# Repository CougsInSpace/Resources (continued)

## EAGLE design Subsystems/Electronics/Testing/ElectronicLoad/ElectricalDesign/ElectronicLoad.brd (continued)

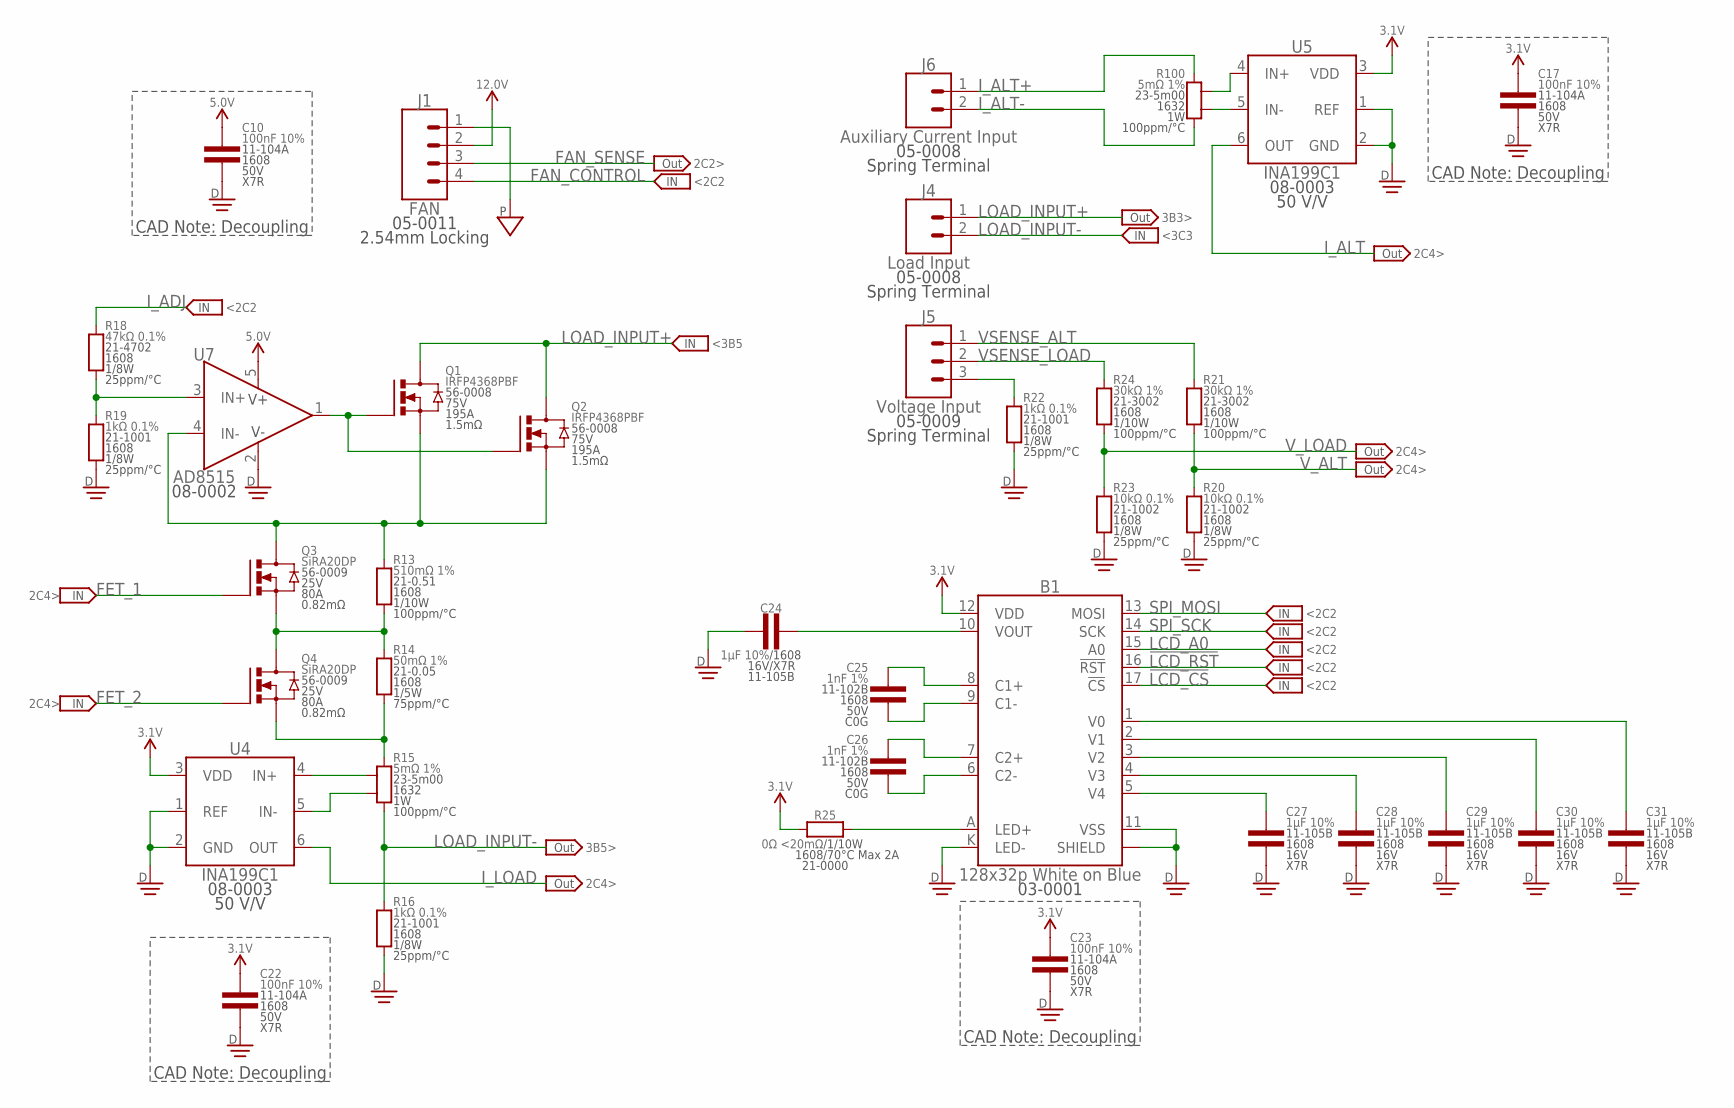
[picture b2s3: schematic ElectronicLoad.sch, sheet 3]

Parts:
B1: 128x32p White on Blue; NHD-C12832A1Z
C10, C17, C22, C23: 100nF 10%; 1608
C24, C27, C28, C29, C30, C31: 1µF 10%; 1608
C25, C26: 1nF 1%; 1608
J1: FAN; THT2.54-1X04-LOCK
J4: Load Input; TERMINAL_SPRING-02
J5: Voltage Input; TERMINAL_SPRING-03
J6: Auxiliary Current Input; TERMINAL_SPRING-02
Q1, Q2: IRFP4368PBF; TO-247-3-DOWN
Q3, Q4: SiRA20DP; POWERPAK-SO-8
R13: 510mΩ 1%; 1608
R14: 50mΩ 1%; 1608
R15, R100: 5mΩ 1%; 1632-KELVIN
R16, R19, R22: 1kΩ 0.1%; 1608
R18: 47kΩ 0.1%; 1608
R20, R23: 10kΩ 0.1%; 1608
R21, R24: 30kΩ 1%; 1608
R25: 0Ω <20mΩ; 1608
U4, U5: INA199C1; SOT363
U7: AD8515; SOT23-5

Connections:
3.1V: B1.12 (VDD), C17.1, C22.1, C23.1, R25.1, U4.3 (VDD), U5.3 (VDD); also elsewhere on the board
5.0V: C10.1, U7.5 (V+); also elsewhere on the board
12.0V: J1.2; also elsewhere on the board
!LCD_CS: B1.17 (!CS); also elsewhere on the board
!LCD_RST: B1.16 (!RST); also elsewhere on the board
C1+: B1.8 (C1+), C25.1
C1-: B1.9 (C1-), C25.2
C2+: B1.7 (C2+), C26.1
C2-: B1.6 (C2-), C26.2
DGND: B1.11 (VSS), B1.CHASSIS@1 (SHIELD), B1.CHASSIS@2 (SHIELD), B1.CHASSIS@3 (SHIELD), B1.CHASSIS@4 (SHIELD), B1.K (LED-), C10.2, C17.2, C22.2, C23.2, C24.1, C27.2, C28.2, C29.2, C30.2, C31.2, R16.1, R19.1, R20.1, R22.1, R23.1, U4.1 (REF), U4.2 (GND), U5.1 (REF), U5.2 (GND), U7.2 (V-); also elsewhere on the board
FAN_CONTROL: J1.4; also elsewhere on the board
FAN_SENSE: J1.3; also elsewhere on the board
FEEDBACK: Q1.3 (S), Q2.3 (S), Q3.5 (D), Q3.6 (D), Q3.7 (D), Q3.8 (D), Q3.PAD (D), R13.2, U7.4 (IN-)
FET_1: Q3.4 (G); also elsewhere on the board
FET_2: Q4.4 (G); also elsewhere on the board
FET_GATE: Q1.1 (G), Q2.1 (G), U7.1 (OUT)
INPUT_SHUNT+: R100.2-KELVIN, U5.4 (IN+)
INPUT_SHUNT-: R100.1-KELVIN, U5.5 (IN-)
I_ADJ: R18.2; also elsewhere on the board
I_ALT: U5.6 (OUT); also elsewhere on the board
I_ALT+: J6.1, R100.2
I_ALT-: J6.2, R100.1
I_LOAD: U4.6 (OUT); also elsewhere on the board
LCD_A0: B1.15 (A0); also elsewhere on the board
LCD_LED: B1.A (LED+), R25.2
LCD_V0: B1.1 (V0), C31.1
LCD_V1: B1.2 (V1), C30.1
LCD_V2: B1.3 (V2), C29.1
LCD_V3: B1.4 (V3), C28.1
LCD_V4: B1.5 (V4), C27.1
LOAD_INPUT+: J4.1, Q1.2 (D), Q1.PAD (D), Q2.2 (D), Q2.PAD (D)
LOAD_INPUT-: J4.2, R15.1, R16.2
OP_AMP_IN: R18.1, R19.2, U7.3 (IN+)
OUTPUT_SHUNT+: R15.2-KELVIN, U4.4 (IN+)
OUTPUT_SHUNT-: R15.1-KELVIN, U4.5 (IN-)
PGND: J1.1; also elsewhere on the board
SHUNT_LOW: Q4.1 (S), Q4.2 (S), Q4.3 (S), R14.1, R15.2
SHUNT_MID: Q3.1 (S), Q3.2 (S), Q3.3 (S), Q4.5 (D), Q4.6 (D), Q4.7 (D), Q4.8 (D), Q4.PAD (D), R13.1, R14.2
SPI_MOSI: B1.13 (MOSI); also elsewhere on the board
SPI_SCK: B1.14 (SCK); also elsewhere on the board
VOUT: B1.10 (VOUT), C24.2
VSENSE_ALT: J5.1, R21.2
VSENSE_GND: J5.3, R22.2
VSENSE_LOAD: J5.2, R24.2
V_ALT: R20.2, R21.1; also elsewhere on the board
V_LOAD: R23.2, R24.1; also elsewhere on the board

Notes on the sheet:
<2C2
2C4>
2C4>
<3B5
3B3>
CAD Note: Decoupling
2C2>
3B5>
<3C3

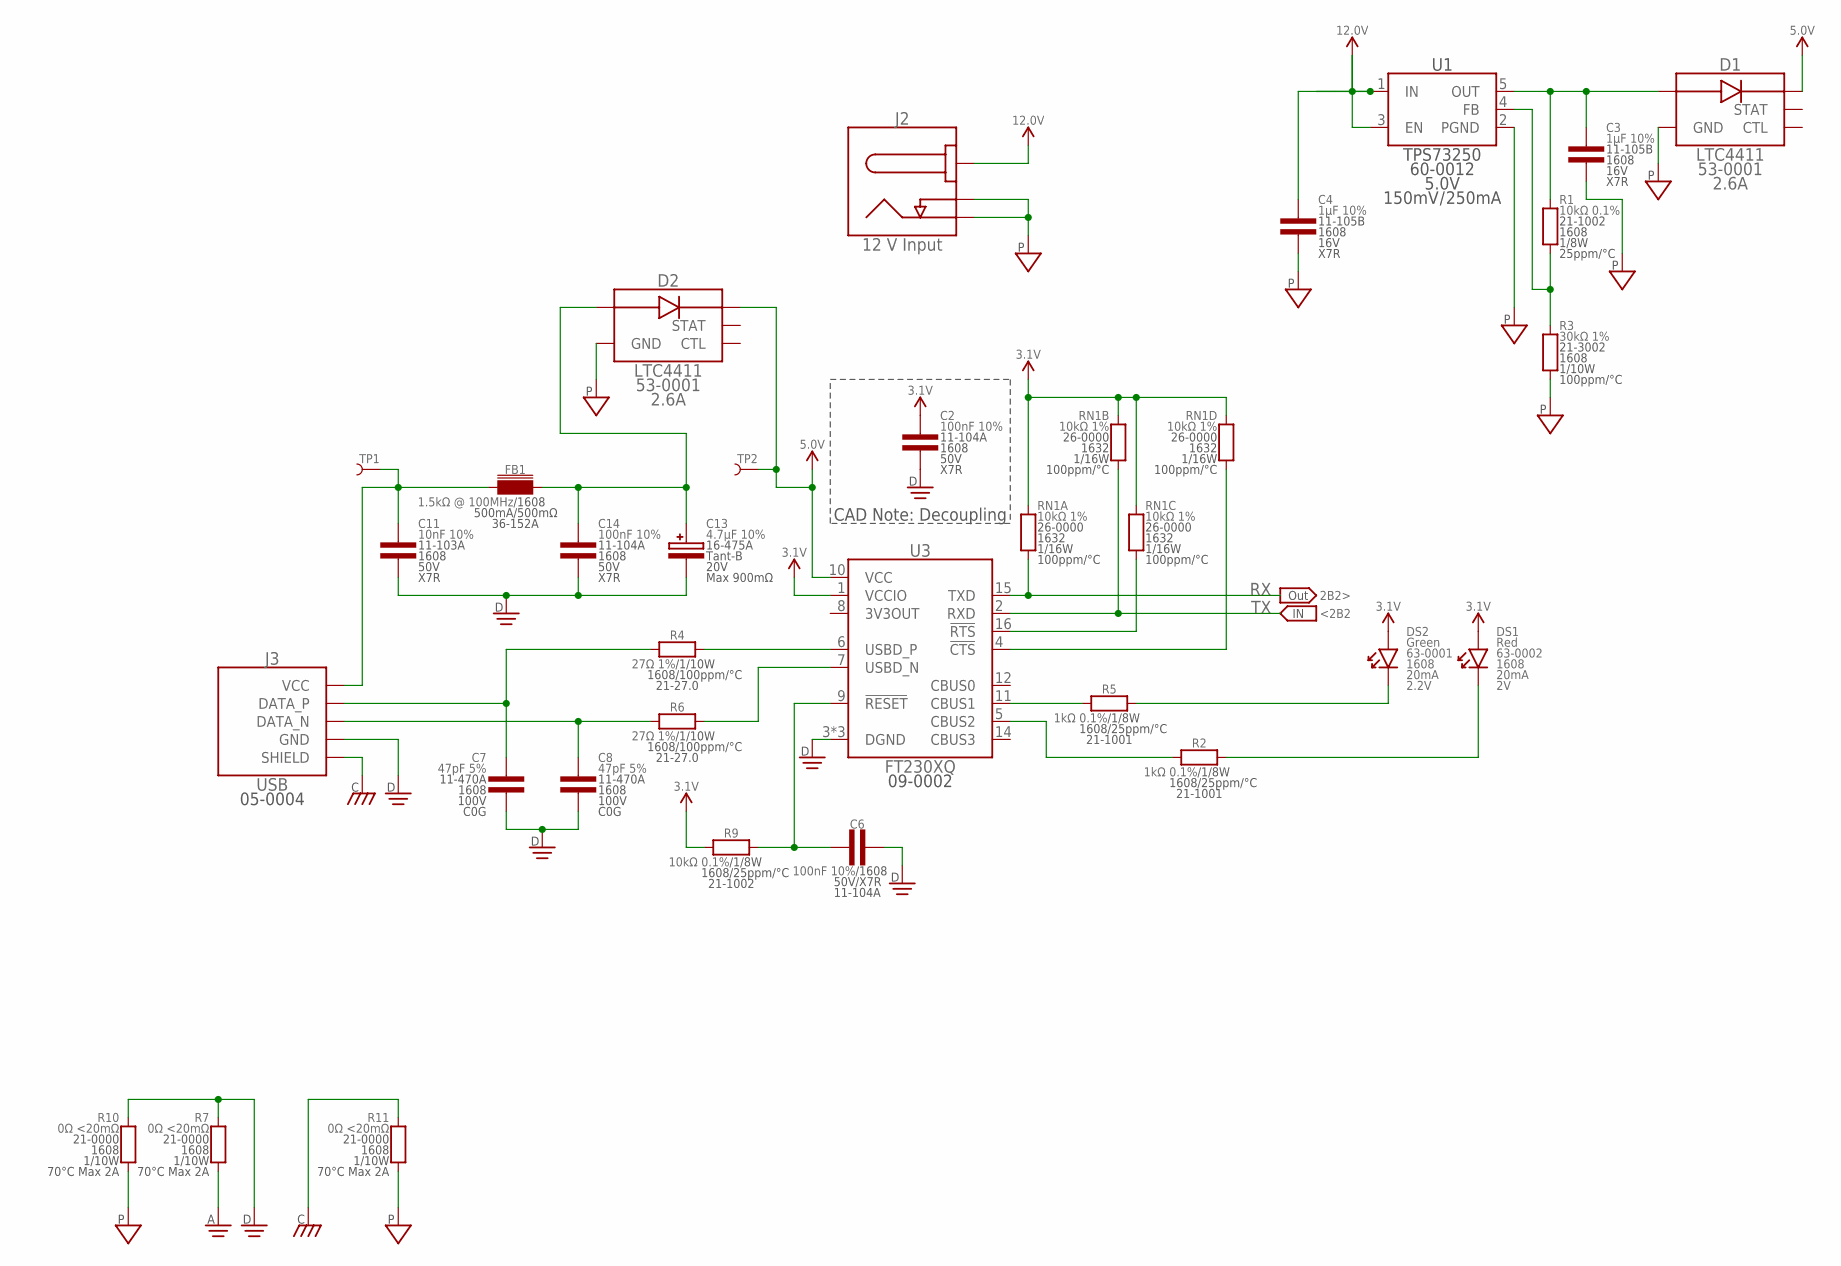
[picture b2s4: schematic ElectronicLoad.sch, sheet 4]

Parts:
C2, C6, C14: 100nF 10%; 1608
C3, C4: 1µF 10%; 1608
C7, C8: 47pF 5%; 1608
C11: 10nF 10%; 1608
C13: 4.7µF 10%; 4028-POL
D1, D2: LTC4411; SOT23-5
DS1: Red; 1608-POL
DS2: Green; 1608-POL
FB1: 1.5kΩ @ 100MHz; 1608
J2: 12 V Input; BARREL-2.1X5.5-R
J3: USB; USB-B-FEMALE
R1, R9: 10kΩ 0.1%; 1608
R2, R5: 1kΩ 0.1%; 1608
R3: 30kΩ 1%; 1608
R4, R6: 27Ω 1%; 1608
R7, R10, R11: 0Ω <20mΩ; 1608
RN1: 10kΩ 1%; 1632
TP1, TP2: TEST_POINT-THT-1.0; THT-1.0
U1: TPS73250; SOT23-5
U3: FT230XQ; QFN-16-4040

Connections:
3.1V: C2.1, DS1.A, DS2.A, R9.1, RN1.5 (2), RN1.6 (2), RN1.7 (2), RN1.8 (2), U3.1 (VCCIO); also elsewhere on the board
5.0V: D1.5 (OUT), D2.5 (OUT), TP2.1, U3.10 (VCC); also elsewhere on the board
12.0V: J2.1 (CENTER); also elsewhere on the board
!CTS: RN1.4 (1), U3.4 (!CTS)
!RTS: RN1.3 (1), U3.16 (!RTS)
AGND: R7.1; also elsewhere on the board
CBUS1: R5.1, U3.11 (CBUS1)
CBUS2: R2.1, U3.5 (CBUS2)
CHASSIS: J3.SHIELD@1 (SHIELD), J3.SHIELD@2 (SHIELD), R11.2; also elsewhere on the board
DGND: C2.2, C6.2, C7.2, C8.2, C11.2, C13.C, C14.2, J3.4 (GND), R7.2, R10.2, U3.3 (DGND), U3.13 (DGND), U3.PAD (DGND); also elsewhere on the board
unnamed: C4.1, U1.1 (IN), U1.3 (EN)
unnamed: C13.A, C14.1, D2.1 (IN), FB1.2
unnamed: C3.1, D1.1 (IN), R1.2, U1.5 (OUT)
unnamed: R1.1, R3.2, U1.4 (FB)
PGND: C3.2, C4.2, D1.2 (GND), D2.2 (GND), J2.2 (SLEEVE), J2.3 (SW), R3.1, R10.1, R11.1, U1.2 (PGND); also elsewhere on the board
RX: RN1.1, U3.15 (TXD); also elsewhere on the board
RXLED_C: DS1.C, R2.2
TX: RN1.2 (1), U3.2 (RXD); also elsewhere on the board
TXLED_C: DS2.C, R5.2
USB5V: C11.1, FB1.1, J3.1 (VCC), TP1.1
USB_CONN_N: C8.1, J3.2 (DATA_N), R6.1
USB_CONN_P: C7.1, J3.3 (DATA_P), R4.1
USB_N: R6.2, U3.7 (USBD_N)
USB_P: R4.2, U3.6 (USBD_P)
USB_RESET: C6.1, R9.2, U3.9 (!RESET)

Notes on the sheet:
CAD Note: Decoupling
2B2>
<2B2

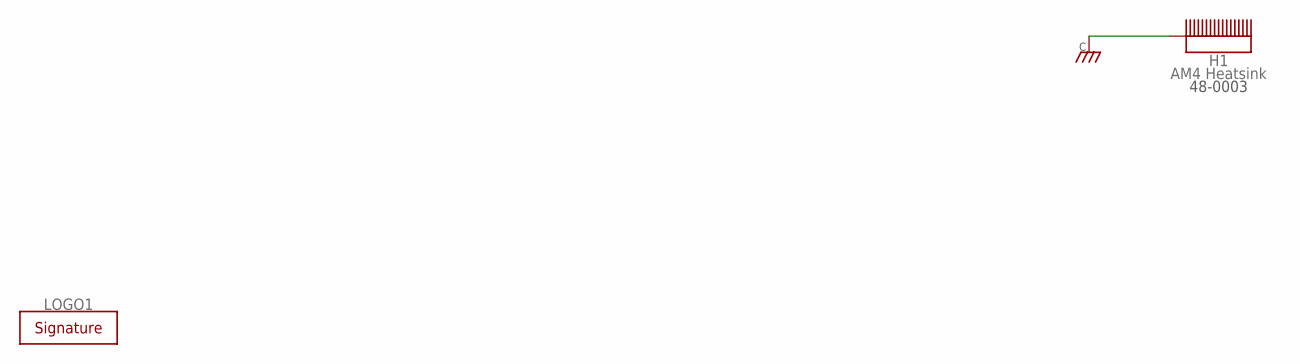
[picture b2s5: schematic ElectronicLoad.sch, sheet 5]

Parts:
H1: AM4 Heatsink; HEATSINK-AM4
LOGO1: SIGNATUREJAYSON; SIGN-JAYSON

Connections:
CHASSIS: H1.1, H1.2, H1.3, H1.4, H1.V1, H1.V2, H1.V3, H1.V4, H1.V5, H1.V6, H1.V7, H1.V8, H1.V9, H1.V10, H1.V11, H1.V12, H1.V13, H1.V14, H1.V15, H1.V16, H1.V17, H1.V18, H1.V19, H1.V20, H1.V21, H1.V22, H1.V23, H1.V24, H1.V25, H1.V26, H1.V27, H1.V28, H1.V29, H1.V30, H1.V31, H1.V32, H1.V33, H1.V34, H1.V35, H1.V36, H1.V37, H1.V38, H1.V39, H1.V40, H1.V41, H1.V42, H1.V43, H1.V44, H1.V45, H1.V46, H1.V47, H1.V48, H1.V49, H1.V50, H1.V51, H1.V52, H1.V53, H1.V54, H1.V55, H1.V56, H1.V57, H1.V58, H1.V59, H1.V60, H1.V61, H1.V62, H1.V63, H1.V64, H1.V65, H1.V66, H1.V67, H1.V68, H1.V69, H1.V70, H1.V71, H1.V72; also elsewhere on the board

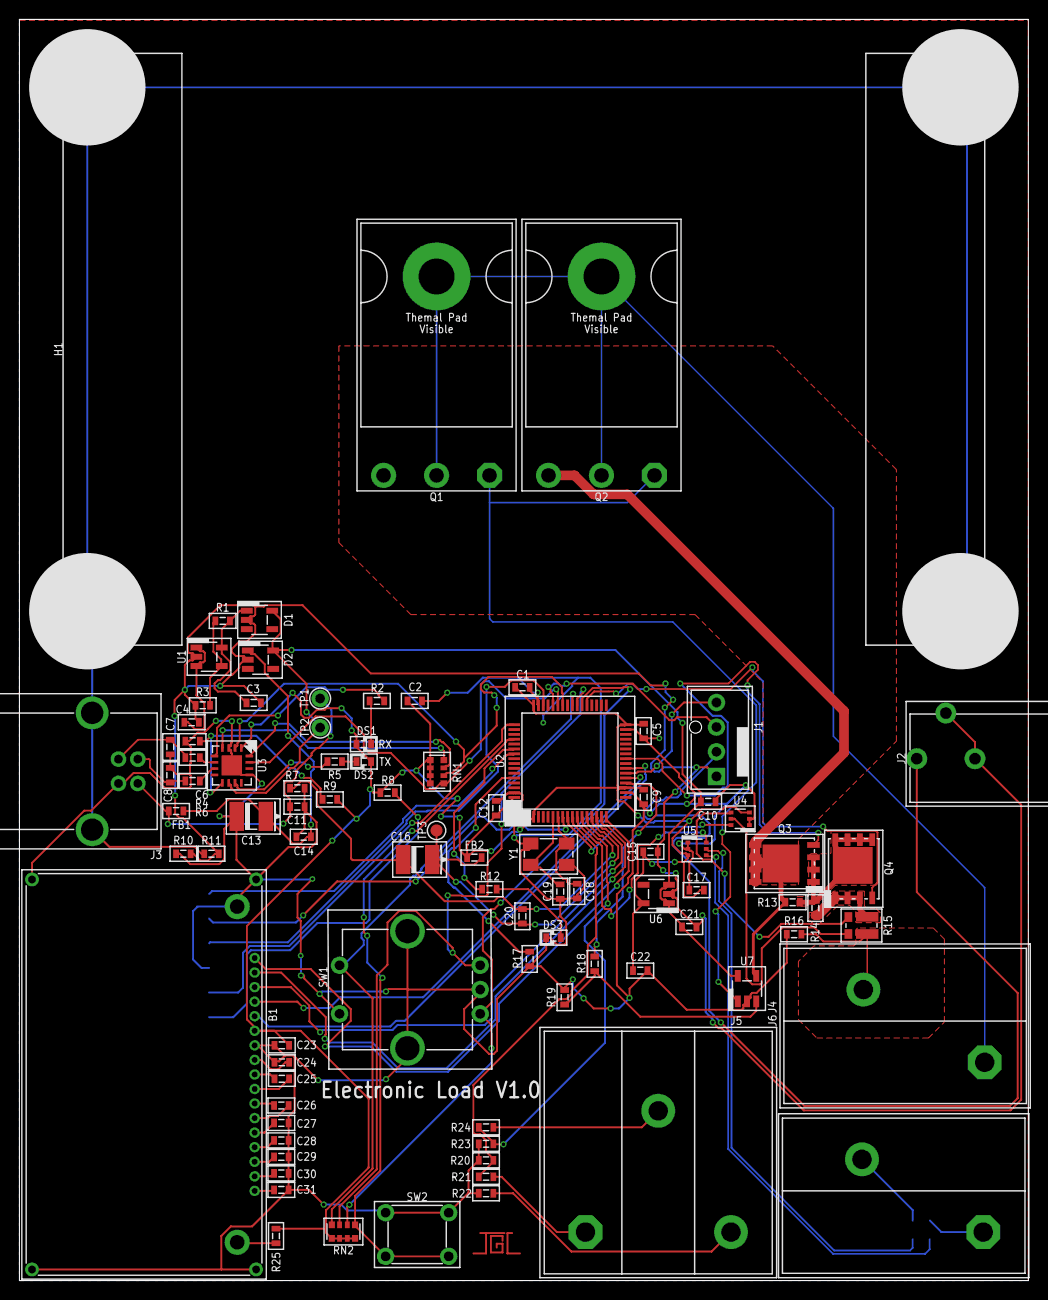
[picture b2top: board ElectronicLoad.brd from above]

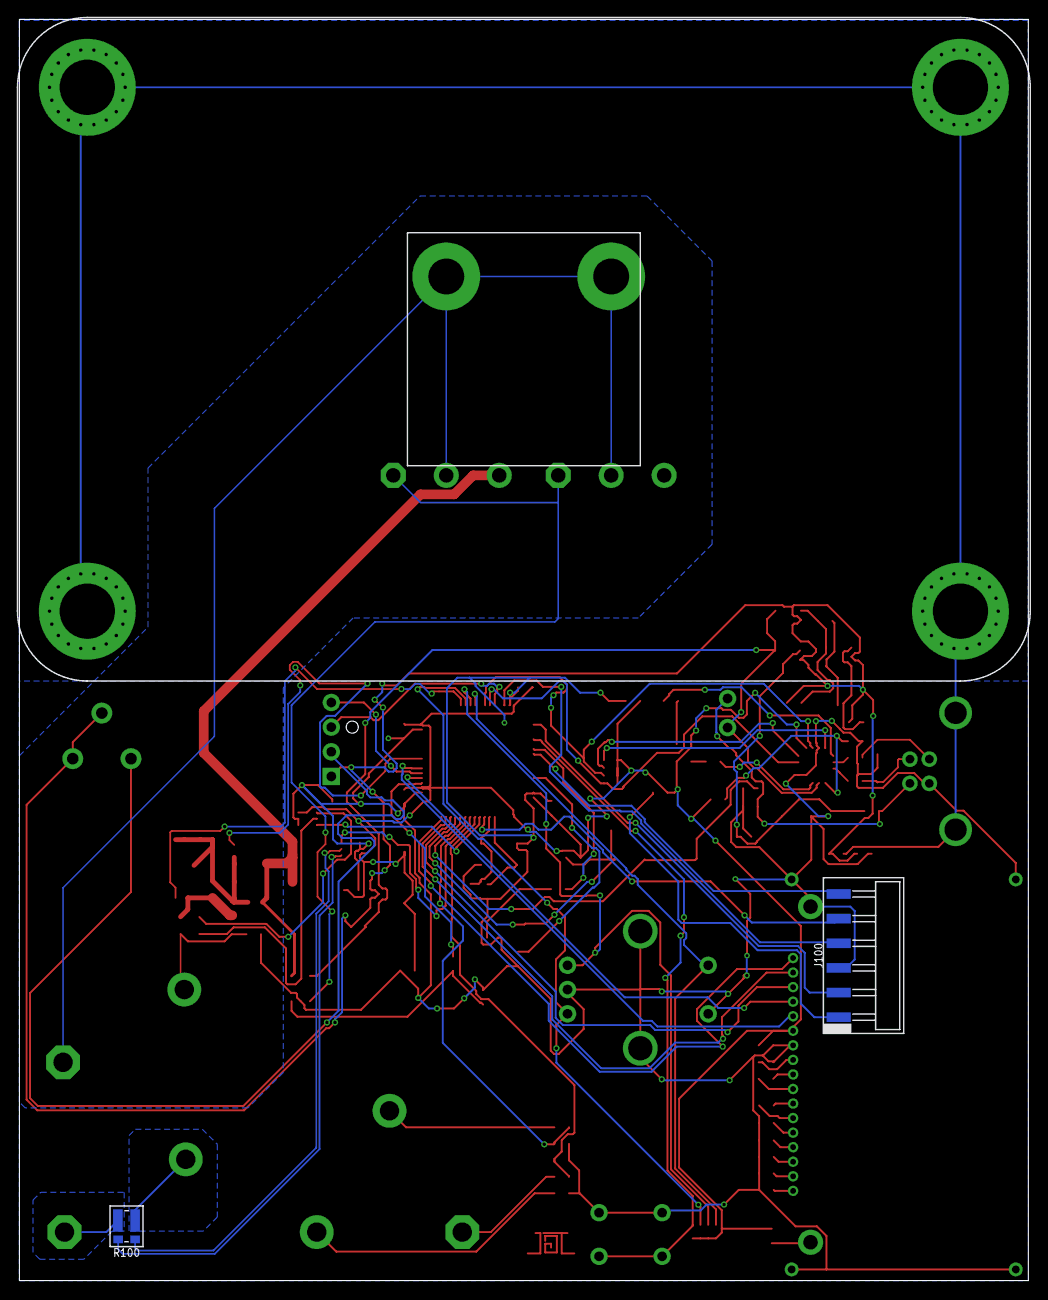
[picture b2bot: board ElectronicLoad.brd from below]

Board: 2 copper layers, 104.0 x 130.0 mm, 93 parts (2 on the bottom side), 81 nets.

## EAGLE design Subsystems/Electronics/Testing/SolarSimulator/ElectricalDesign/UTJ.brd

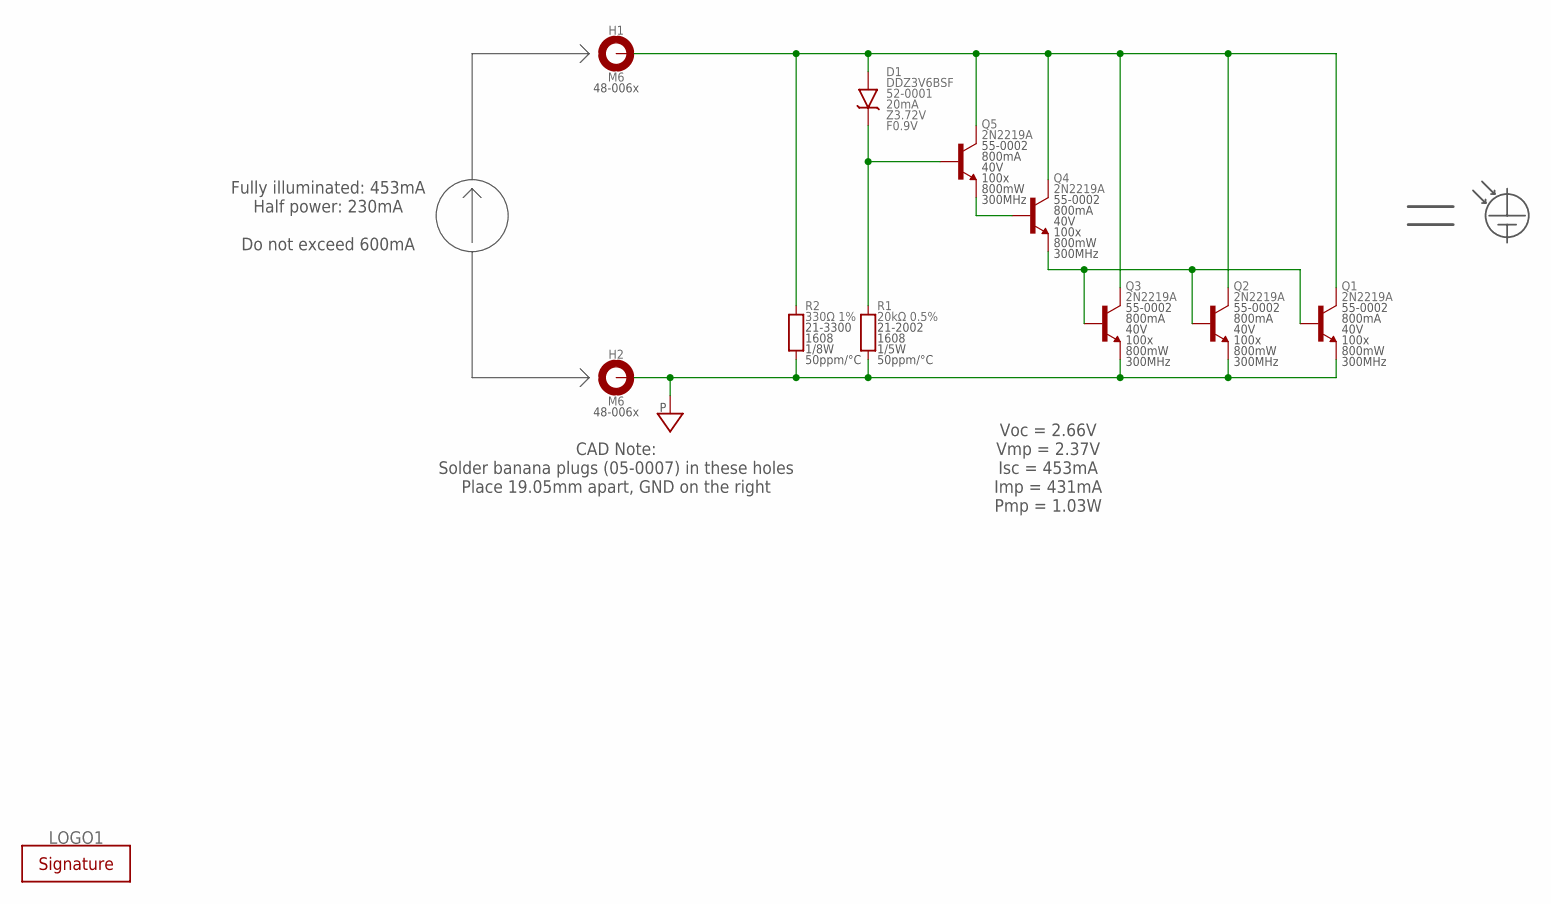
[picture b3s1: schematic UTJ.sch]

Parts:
D1: DDZ3V6BSF; SOD323F
H1, H2: M6; MOUNTING_HOLE-6.6
LOGO1: SIGNATUREBRADLEY; SIGN-BRADLEY
Q1, Q2, Q3, Q4, Q5: 2N2219A; TO-39
R1: 20kΩ 0.5%; 1608
R2: 330Ω 1%; 1608

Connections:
CELL+: D1.A, H1.1, H1.V1, H1.V2, H1.V3, H1.V4, H1.V5, H1.V6, H1.V7, H1.V8, H1.V9, H1.V10, H1.V11, H1.V12, H1.V13, H1.V14, H1.V15, H1.V16, Q1.3 (C), Q2.3 (C), Q3.3 (C), Q4.3 (C), Q5.3 (C), R2.2
EMITTER-1: Q4.2 (B), Q5.1 (E)
EMITTER-2: Q1.2 (B), Q2.2 (B), Q3.2 (B), Q4.1 (E)
PGND: H2.1, H2.V1, H2.V2, H2.V3, H2.V4, H2.V5, H2.V6, H2.V7, H2.V8, H2.V9, H2.V10, H2.V11, H2.V12, H2.V13, H2.V14, H2.V15, H2.V16, Q1.1 (E), Q2.1 (E), Q3.1 (E), R1.1, R2.1
ZENER_C: D1.C, Q5.2 (B), R1.2

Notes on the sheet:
Fully illuminated: 453mA Half power: 230mA Do not exceed 600mA
Voc = 2.66V Vmp = 2.37V Isc = 453mA Imp = 431mA Pmp = 1.03W
CAD Note: Solder banana plugs (05-0007) in these holes Place 19.05mm apart, GND on the right

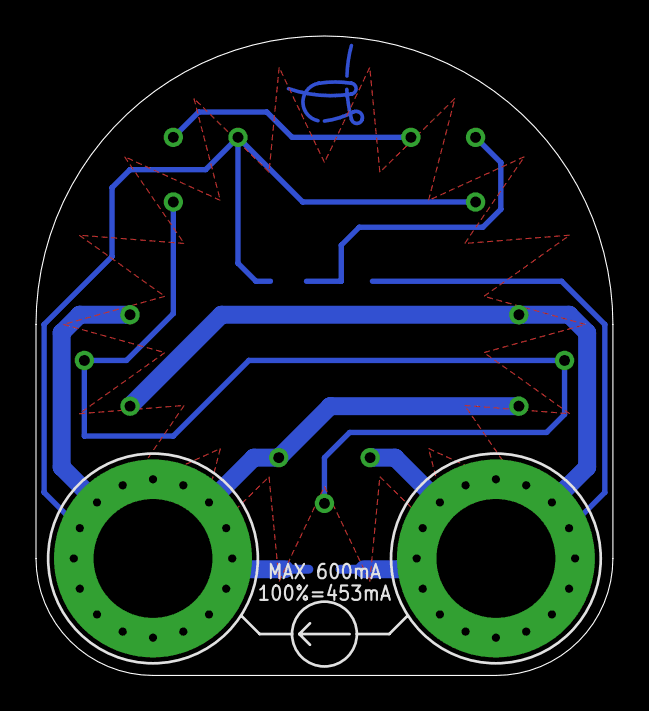
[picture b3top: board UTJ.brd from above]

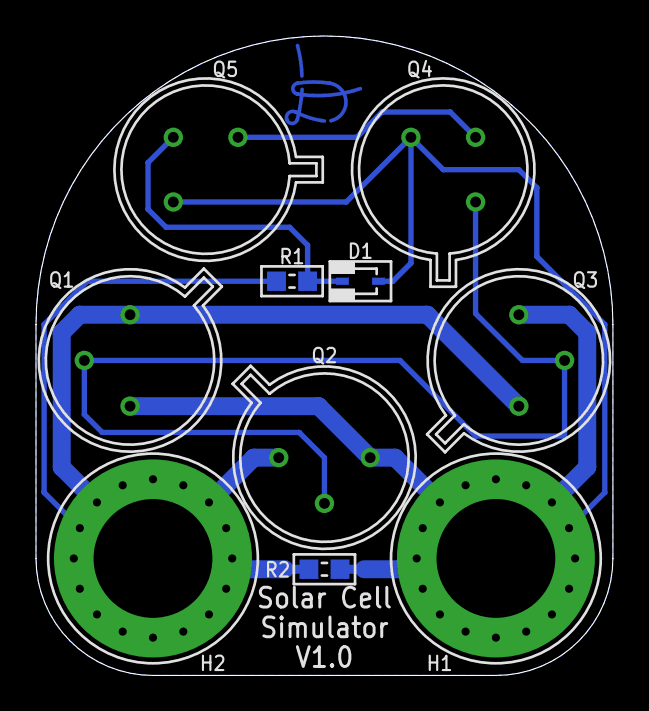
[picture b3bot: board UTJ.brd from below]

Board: 2 copper layers, 32.0 x 35.5 mm, 11 parts (9 on the bottom side), 5 nets.

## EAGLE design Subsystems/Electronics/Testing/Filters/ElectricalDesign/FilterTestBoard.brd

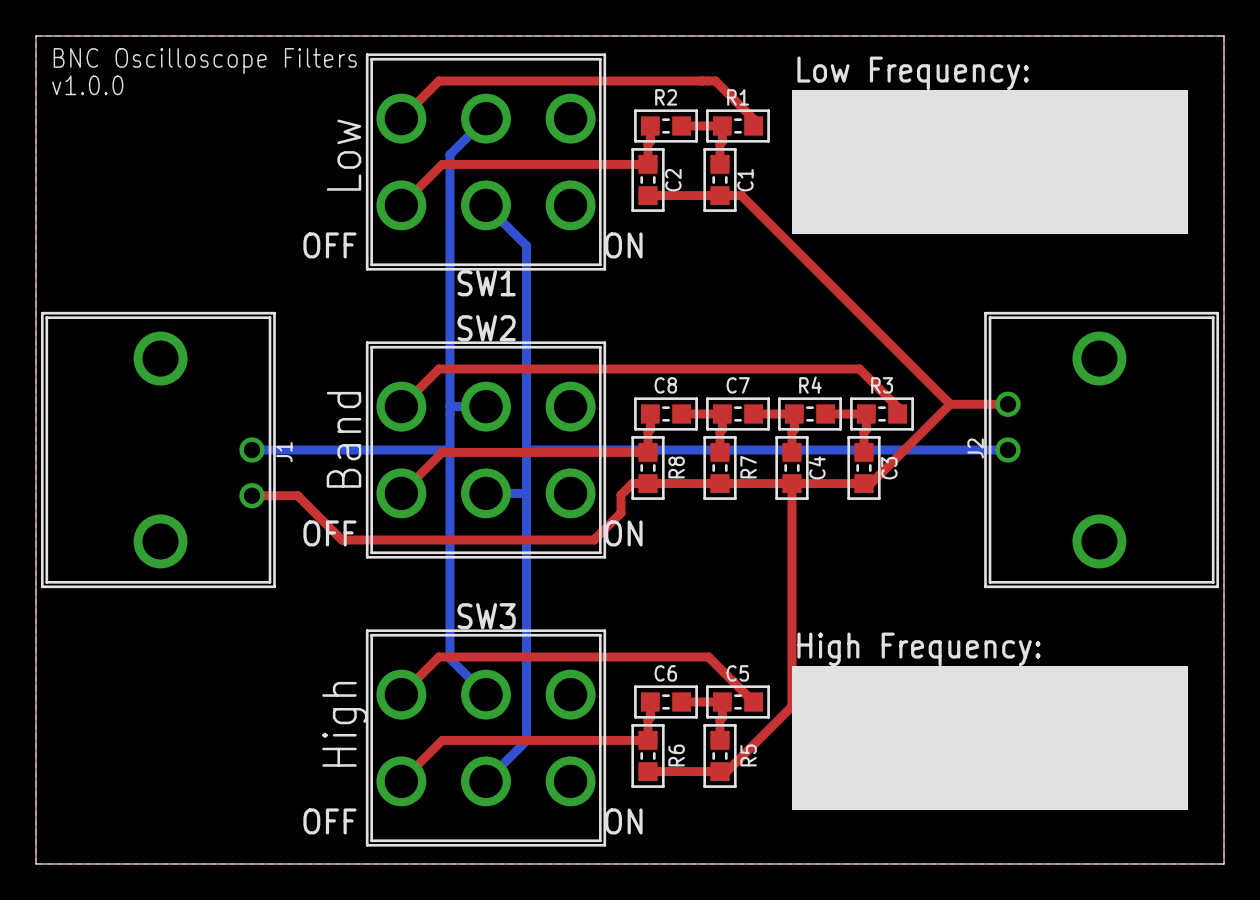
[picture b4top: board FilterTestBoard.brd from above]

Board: 2 copper layers, 66.0 x 46.0 mm, 21 parts (0 on the bottom side), 14 nets.

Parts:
C1, C2, C3, C4, C5, C6, C7, C8: 10µF 10%; 1608
J1, J2: BNC-T-R
R1, R2, R7, R8: 158kΩ 0.1%; 1608
R3, R4, R5, R6: 158Ω 1%; 1608
SW1, SW2, SW3: 100DP1T1B1M2QE

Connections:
BAND_IN: R3.1, SW2.1-B
BAND_INT0: C3.1, R3.2, R4.1
BAND_INT1: C4.1, C7.1, R4.2
BAND_INT2: C7.2, C8.1, R7.2
BAND_OUT: C8.2, R8.2, SW2.1-A
HIGH_IN: C5.1, SW3.1-B
HIGH_INT: C5.2, C6.1, R5.2
HIGH_OUT: C6.2, R6.2, SW3.1-A
INPUT: J1.CENTER, SW1.COM-B, SW2.COM-B, SW3.COM-B
LOW_IN: R1.1, SW1.1-B
LOW_INT: C1.1, R1.2, R2.1
LOW_OUT: C2.1, R2.2, SW1.1-A
OUTPUT: J2.CENTER, SW1.COM-A, SW2.COM-A, SW3.COM-A
PGND: C1.2, C2.2, C3.2, C4.2, J1.SHIELD, J2.SHIELD, R5.1, R6.1, R7.1, R8.1

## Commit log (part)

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2018-04-08 Added Documents
2018-04-12 Updated Header Boxes Layout
2018-04-13 Readme.txt
2018-05-12 Updated Template
2018-05-13 Added Components
2018-05-18 Added Empty Libraries
2018-05-18 Update README.md
    Changed silkscreen line width
2018-05-19 Added Aesthetic Parts
2018-05-19 Added Energy Parts
2018-05-19 Added Signatures
2018-05-20 Added Clocks
2018-05-21 Added Coils
2018-05-21 Added Connectors
2018-05-22 Added Discrete Semiconductors
2018-05-22 Added Fuses
2018-05-22 Added Amplifiers, Comms, & Conversion ICs
    Also fixed some packages' name layer
2018-05-22 Added Logic ICs
2018-05-22 Added Memory
2018-05-22 Added Switches
2018-05-23 Added Power ICs
2018-05-23 Added µControllers
2018-05-23 Added Sensors and a Logic IC
2018-05-24 Added Resistors, RF, LEDs, and Horizontal Symbols
2018-05-24 Added Eagle Guidelines Readme
2018-05-25 Adjusted Title Block and Courtyard
2018-05-25 Updated Title Block Image
2018-05-25 Added Off Sheet Connector Image for Readme
2018-05-27 Added Diagram Components
2018-05-27 Added Through Hole Test Points
2018-05-29 Added PicoLock Connectors
2018-05-30 Added Bolts and TO220 Resistor
2018-05-31 readme
2018-06-01 SDS sheets for current EME 107 lab chemicals
2018-06-03 Added CougSat Bus Symbol
2018-06-04 Added Umbilical Connector
2018-06-05 Adjusted Packages
2018-06-05 Added SWD Connector
2018-06-10 Added Jumper
2018-06-10 Added Dual MOSFETs
2018-06-28 Created Project Management SOP
2018-06-28 Fixed Missing Punctuation
2018-06-28 added file manager script
2018-06-28 Delete README
    will make new one
2018-07-04 Created Inventor Templates
2018-07-17 Added Component Models and Updated Eagle Library Font
2018-07-20 added file deletion functionality
2018-07-22 Added Parts
2018-07-22 Added Acronyms
2018-07-22 Adjusted Symbol Layout
2018-07-23 Fixed Readme Link
2018-07-24 Removed ± Symbol From Temperature Coefficient
2018-07-29 Added Component Models
2018-08-01 Removed Version Numbers from PDFs
2018-08-25 Added Bussed Resistor Network
2018-09-07 Updated EAGLE Guidelines
2018-09-12 Added 8.45kΩ Resistor
2018-09-13 Added Magnetorquer
2018-09-17 Updated Backplane Pins and Package
2018-09-24 Added GPS Datasheet to ADCS Resources area
2018-09-27 Added Servo Model
2018-09-29 Moved Attribute and Updated CAM
2018-09-29 Added mCAD for EPS Components
2018-10-01 Added Automatic Numbering to Headings
2018-10-06 Added Logic Level Shifter
2018-10-06 Added U.FL Connector
2018-10-08 Moved Inventory to Google Drive
2018-10-09 Changed Solar Cell Package
2018-10-21 Added GPS Antenna and Antenna Parts
2018-10-22 Added a Switch and BNC
2018-10-22 Added RF ICs and Shielding
2018-10-24 Adjusted Formatting
2018-10-24 Created Schematic for Filter Test Board
2018-10-25 Laid out Board
2018-10-25 Changed Routing
2018-10-26 Adjusted Board Layout
2018-10-28 Created Gerbers
2018-10-28 Exported Schematics
2018-11-05 Added MOSFET Variant
2018-11-06 Added Thermal Pads
2018-11-07 Added Spring Loaded Contact and Updated Micro Switch Datasheet
2018-11-10 Added USB and Barrel Connectors
2018-11-11 Added STM32L496RG
2018-11-11 Added USB UART Bridge
2018-11-11 Added Resistors and Capacitors
2018-11-12 Added 10Ω 1608
2018-11-12 Added Power Symbols Channels
2018-11-15 Added 1µH Inductor
2018-11-23 Added OpAmps and Regulators
2018-11-24 Added RF Amplifiers
2018-11-24 Added RF LNA
2018-11-24 Added LDO
2018-11-25 Added RF Switch and nFETs
2018-11-27 Added Documentation
2018-12-01 Added Shields, Adjusted Solar Cell Package
2018-12-04 Updated Word Template for Heading Layer 4
2018-12-09 Added CAM and ULPs
2018-12-15 Adjusted 1608 Package and Added Flash Memory
2019-02-02 Changed Pin Direction and Fixed Value Typo
2019-02-04 Added mCAD for Library Components
2019-02-05 Added Lever Microswitch and Fasteners
2019-02-06 Added 3.3V LDO
2019-02-17 Fixed Voltage Rating and SKU
2019-02-26 Updated CougSat Card and mCAD
2019-04-01 Updated mCAD
2019-04-06 Refactored Supplier Documents
2019-04-07 Changed Coax Font Size
2019-05-02 Source code from CptS423
2019-05-02 Added final report
2019-05-02 Removed broken dirs
2019-05-02 Recommit, src and docs from CptS423
2019-05-19 Updated signature (Hendrik), removed HAM
2019-05-19 Adjusted annular ring size on 1mm test point
2019-06-22 Added TPS2115A
2019-06-22 Added SMD right angle switch
2019-06-23 Added 33nH inductor
2019-06-26 Added ADC and current sense amplifier
2019-06-27 Added AD7689
2019-07-01 Added kelvin connection resistors, ideal diode, and current sense amplifier
2019-07-02 Designed solar cell simulator circuit
2019-07-02 Laid out solar simulator
2019-07-07 Exported Gerbers
2019-07-12 Fixed pin names and directions
2019-07-13 Adjusted THT diameters and added 750Ω resistor datasheet
2019-07-27 Added GPS patch antenna silkscreen
2019-07-27 Added gitkeep to each sku folder
2019-07-29 Adjusted pad diameters
2019-08-08 Added ionizing radiation sensor
2019-08-08 Added ArduCam
2019-08-14 Added Jayson's signature
2019-08-15 Added avref-2
2019-08-19 Adjusted footprints and pin 1 markers
2019-08-21 Adjusted footprints
2019-08-26 Added 8MHz crystal
2019-08-27 Adjusted silkscreen
2019-08-30 Added parts for gamma ray detector
2019-09-03 Added Power MOSFET 56-0009 and TO247 Horizontal Package
2019-09-08 Created Block Diagram
2019-09-08 Addressed Feedback
2019-09-08 Fixed formatting, removed bad file
2019-09-08 Created Electronic Load Software Project
2019-09-12 Adjusted annular ring
2019-09-14 Added spring terminal blocks
2019-09-15 Added a Schematic
2019-09-15 Added rotary encoder with nice knob
2019-09-16 Added tactile switch with cap
2019-09-21 Moved mCAD for 01 through 10
2019-09-22 Electronic_Load_Current_Path
    Added all of the known pins to the software along with the current input/output and voltage input/output pathing.
2019-09-23 Adjusted Jayson's signature width
2019-09-29 Added 0.51ohm resistor
2019-09-29 Electronic Load Current Control
    Updated the code for the current control and is now ready for review
2019-09-30 Added mCAD for all parts
2019-10-06 Voltage and Current Monitoring
    Implemented the voltage and current monitoring to finish this weeks issue and completed all of the requested changes form the Electronic_Load_Current_Path issue.
2019-10-06 Fixed Spacing and Deleted Main Function Header
2019-10-07 Added 08-0006
2019-10-09 Adjusted solar cell footprint
2019-10-22 Adjusted silkscreeen and added lens holder
2019-10-26 Added 42-136A
2019-10-27 Added 27-0005
2019-10-27 Added 65-0011
2019-10-29 Added resistors
2019-10-30 Added 27-0006
2019-10-30 Added capacitors and inductors for RF filters
2019-11-03 Added 230mm amplifiers and their passives
2019-11-04 Added reverse calculations for thermistor
2019-11-10 Implemented Nice Knob
    QEI for nice knob has been added along with push function and button push. Changed appropiate/known PINs.
2019-11-11 Electronic Load (Hopefully Im done now)
2019-11-21 Adjusted silkscreen, added RF shields
2019-12-08 Added the code for the LCD screen
    The LCD screen header files for font and the C++ code for the LCD screen labeled as LCD.cpp LCD.h and LCDfont.h have all been acquired, altered, and added. Also, removed a useless function from the m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
2019-12-19 Added decapaps, fixed formatting
2019-12-19 Removed VS files
2020-01-26 Added 12V symbol
2020-01-27 Added NCR18650B
2020-01-28 Added heatsink
2020-01-30 Fixed it part (100,000,000)
2020-01-30 Added White LED
    added led and copied .ipt
2020-01-30 Updated LED Library with White LED
2020-01-31 Added LDO, Fixed Formatting
2020-01-31 Added 66-0008
2020-01-31 Updated BME 280 Sensor Description
2020-02-01 Moved documentation
2020-02-02 Added 27-0007
2020-02-07 Prototyped layout
2020-02-07 Added 23-0000
2020-02-13 Added 49-0006
2020-02-17 Added low profile screws
2020-02-21 Added Josh's signature
2020-02-21 Adjusted 1.5mm hole annular ring
2020-02-27 Created calculator for wire temperature
2020-02-28 Fixed mCAD interferences
2020-02-28 Moved PCIe orgin to the slot (0.15mm offset from hole)
2020-03-01 Layout is done
2020-03-09 index on master: b9b740f Merge pull request #47 from CougsInSpace/electronic-load
2020-03-09 Implemented Things
    Implemented LCD screen and implemented the NICE Knob too. Added functionality for each in main and function calls
2020-03-13 Update to main.cpp
    Fixed values, improved compiling time, and added comments
2020-03-15 Formatted files, removed database file
2020-10-27 Layout_placement
2020-11-07 FIxes_to_layout
2020-11-26 Updated board layout
2020-12-17 modified-layout
2021-02-02 Removed paste on card fingers
2021-02-09 worked on layout
2021-03-11 Board Layout finished
2021-05-29 Finished board layout
2021-09-12 Updated knob
2021-09-26 updated voltage and power
2021-09-26 Fixed build system
2021-09-26 Fixed Build Errors
2021-10-03 Wrote Fan Class
2021-10-03 Created a Menu
2021-10-11 Added test instructions
2021-10-13 Updated Menu
2021-10-26 Created Gabe's signature
2021-10-28 Updated tests
2021-10-31 Menu interaction with resistance and current.
    Fixed the bypass shunts, Created a set Resistance, to interact with the menu. Now we need the Power setter
2021-10-31 Set current with a power input.
2021-10-31 Commit before test on board
    Instantiated fan and menu in the main function.
2021-11-11 display
2021-11-14 Updated Orion part
2021-11-17 Added Orion B16
2021-11-17 Adjusted 03-0002 library model and made mCAD
2021-12-06 Refactored and tested control loop
2021-12-23 Adjusted mCAD
2022-01-30 Finished mosfet testing
2022-02-07 Finished Test
2022-03-27 updated shunt resistor value
2022-10-09 Updated CubeSat Design Specifications Revision 14.1
2022-10-09 added document
2022-10-09 added simulation
2022-10-09 added eagle board file
2022-10-10 updated schematics
2022-10-11 added esp chip
2022-10-17 Added Relevant Files for P-Pod
    Added two PDF's regarding P-Pod & updated Readme with more information.
2022-10-18 Updated Readme
    Changed Title
2022-10-20 Added Relevant P-Pod Information
    Added Nanoracks P-Pod equivalent & updated Readme
2022-10-20 Added Regulation Documentation
    Added regulation documents relating to the proposed arc thruster & updated. Added Readme
2022-11-06 Updated main page
2022-12-31 Fixed shorted thermal pad
2023-01-22 General Battery Charger Schematic
    Majority of components placed, absent items not in CIS components library. Many labels missing.
2023-01-22 Partial changes
    1/22/23
2023-01-22 Added USB Charger Component to Library
    did it
2023-01-22 Added 2 ohm resistor
2023-01-23 Finished Switching and Battery Protection Circuits
    Pages 1-3 are basically finished, while the main components for page 4 have been imported
2023-01-29 USB to UART IC Added
    Page 4 should now be complete with the implementation of a USB to UART program converter. ESP32 has been moved to page 5 and outside of the thermistor connection on the charge controller, this should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
2023-01-29 Finished Battery Charger V1
    Will add programmable RGB LEDS at some point, and may update at a later date with an LED display, but otherwise this can be considered the base design for the over-engineered battery charger
2023-01-30 Added RGB LEDs
    Final touches for V1 including CAD notes and addressable LEDs have been added
2023-02-02 Tidied Up Schematic
    Named all major nets, formatted in and out markings to match other CIS schematics, and adjusted LED colors to match convention.
2023-02-04 Create AMSAT-IARU_Link_Model_CougSat1_ver_1.0.0.xls
    It is for the final part of the paper work and we need to have it saved and available on our site.
2023-02-12 Completed Board Layout
    Completed board layout, ready for review. Sense resistors were adjusted from 20m to 25m Ohm. Additional sense pins added.
2023-02-19 Fixed Issues
    Fixed some voltage level issues found while writing the documentation
2023-03-06 Added Signature
    Added personal (Zachary) signature to library, schematic, and board. Also added LED color code text to physical board
2023-03-26 Removed Wire Stubs
    Ran DRC a dozen times and cleaned up all the errors and wire stubs
2023-04-17 Added Truth Table
    Cleaned up the documentation folder and added the truth table for the LED colors. This ensures an official link in preparation for pushing the documentation.
2023-04-17 Added Documentation
    All documentation files have been added
2023-08-27 Added ReadME and new File
2023-08-27 More Changes to Readme
2023-08-28 Readme Mods
2023-08-28 More Mods
2023-08-28 Renamed
2023-08-28 Added Some Folders
2023-08-28 Added More rand Files
2023-09-10 Documentation Instructions Uploaded
2024-02-11 Added Fusion 360 Folder
2024-02-11 added readme
